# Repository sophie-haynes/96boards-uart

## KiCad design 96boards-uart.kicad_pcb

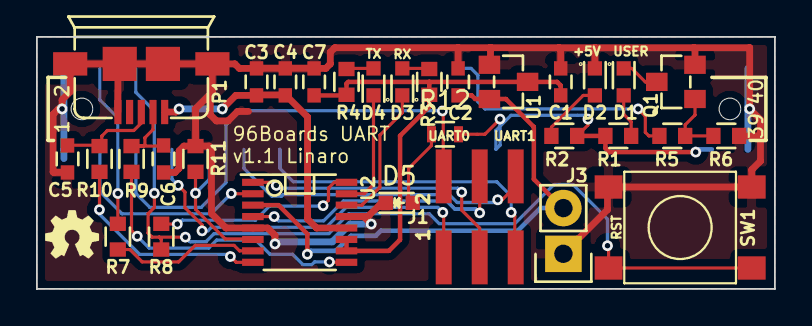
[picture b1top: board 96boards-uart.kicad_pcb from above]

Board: 2 copper layers, 41.0 x 14.0 mm, 32 parts (1 on the bottom side), 31 nets.

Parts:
C1, C2, C3: 1uF; C_0603
C4, C7: 100nF; C_0603
C5, C6: 39pF; C_0603
D1: USER; LED-0603
D2: +5V; LED-0603
D3: RX; LED-0603
D4: TX; LED-0603
D5: 3.2V; LED-0603
J1: CONN_02X03; Pin_Header_SMD_2x03_Pitch2mm
J2: CONN_20X2; Socket_Strip_SMD_2x20_Pitch2mm
J3: CONN_01X02; Pin_Header_Straight_1x02
P1: USB_MICRO_B_ST-USB-001E
Q1: S8050; SOT-23_Seeed
R1: 390R; R_0603_Seeed
R2: 620R; R_0603_Seeed
R3, R4, R7, R8: 220R; R_0603_Seeed
R5: 1k; R_0603_Seeed
R6, R11: 10k; R_0603_Seeed
R9, R10: 22R; R_0603_Seeed
R12: 90Ω; R_0603
SW1: RST; SW_PUSH_DTSM_62K
U1: REG_1.8V; SOT-23_Seeed
U2: FT230XS-R; SSOP-16_3.9x4.9mm_Pitch0.635mm_Seeed

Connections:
+1V8_FTDI: C2.1, J3.2, U1.2, U2.3
+3V3_FTDI: C1.1, C7.1, R3.1, R4.1, U1.3, U2.10, U2.11
CBUS0: D4.1, U2.15
CBUS1: D3.1, U2.14
CBUS2: R7.1, U2.7
CBUS3: R8.1, U2.16
CTS0: J2.3, U2.2
GND: C1.2, C2.2, C3.2, C4.2, C5.2, C6.2, C7.2, D2.1, D5.1, J2.1, J2.2, J2.39, J2.40, J3.1, P1.5, P1.6, P1.7, P1.8, P1.9, Q1.2, R6.2, R11.2, SW1.2, U1.1, U2.5, U2.13
GPIOB: J2.24, R5.1
GPIOC: J2.25, J2.37, R1.1, R2.1, R12.2
unnamed: C5.1, P1.3, R10.1
unnamed: C6.1, P1.2, R9.1
unnamed: D1.1, Q1.3
unnamed: D1.2, R1.2
unnamed: D2.2, R2.2
unnamed: D3.2, R3.2
unnamed: D4.2, R4.2
unnamed: D5.2, R12.1
unnamed: J2.4, R7.2
unnamed: J2.6, R8.2, SW1.1
unnamed: Q1.1, R5.2, R6.1
unnamed: R9.2, U2.9
unnamed: R10.2, U2.8
RTS0: J2.9, R11.1, U2.6
RXD: J1.3, U2.1
RXD0: J1.1, J2.7
RXD1: J1.5, J2.13
TXD: J1.4, U2.4
TXD0: J1.2, J2.5
TXD1: J1.6, J2.11
VBUS: C3.1, C4.1, P1.1, U2.12

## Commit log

2015-08-26 Addition of LED to circuit. Connected to GPIO-C. Might be incorrect :D
2015-08-26 Addition of PCB layout
2015-08-26 PCB Layout
2015-08-26 Gerber files
